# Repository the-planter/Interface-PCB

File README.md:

# Planter Interface PCB

Interface PCB for an automated hydroponics system, created using KiCad 6.0. 

This PCB enables control and interfacing a Raspberry with several liquid level sensors, 12V peristaltic pumps, a few temperature sensors, and remote controllable outlets.

This PCB acts as a carrier board for various off-the-shelf breakout boards. It enables noise-free signals, painless testing, and robust interfacing of the liquid level sensors, peristaltic pumps, air & water temperature sensors, and electrical outlets. Standardized connector types are used to guarantee secure connections; connector types are differentiated by their purpose and voltage level, to ensure no mismatch between components and voltage levels occur. The use of breakout boards alleviates the difficulties in procuring discrete Integrated Circuits (ICs) during the ongoing chip shortage. 

## Manufactured board

| Left View | Right View |
| :---: | :---: |
|  |  |

Hooked up to all sensors:

## Renders

## Routing

## Mechanical Team's Enclosure
The PCB is placed in the top shelf of the enclosure designed by the Mechanical Team

## Schematic

## Repo Setup
- Setup KiCad 6.0 using my [kicad-libraries](https://github.com/AbhinavA10/kicad-libraries)

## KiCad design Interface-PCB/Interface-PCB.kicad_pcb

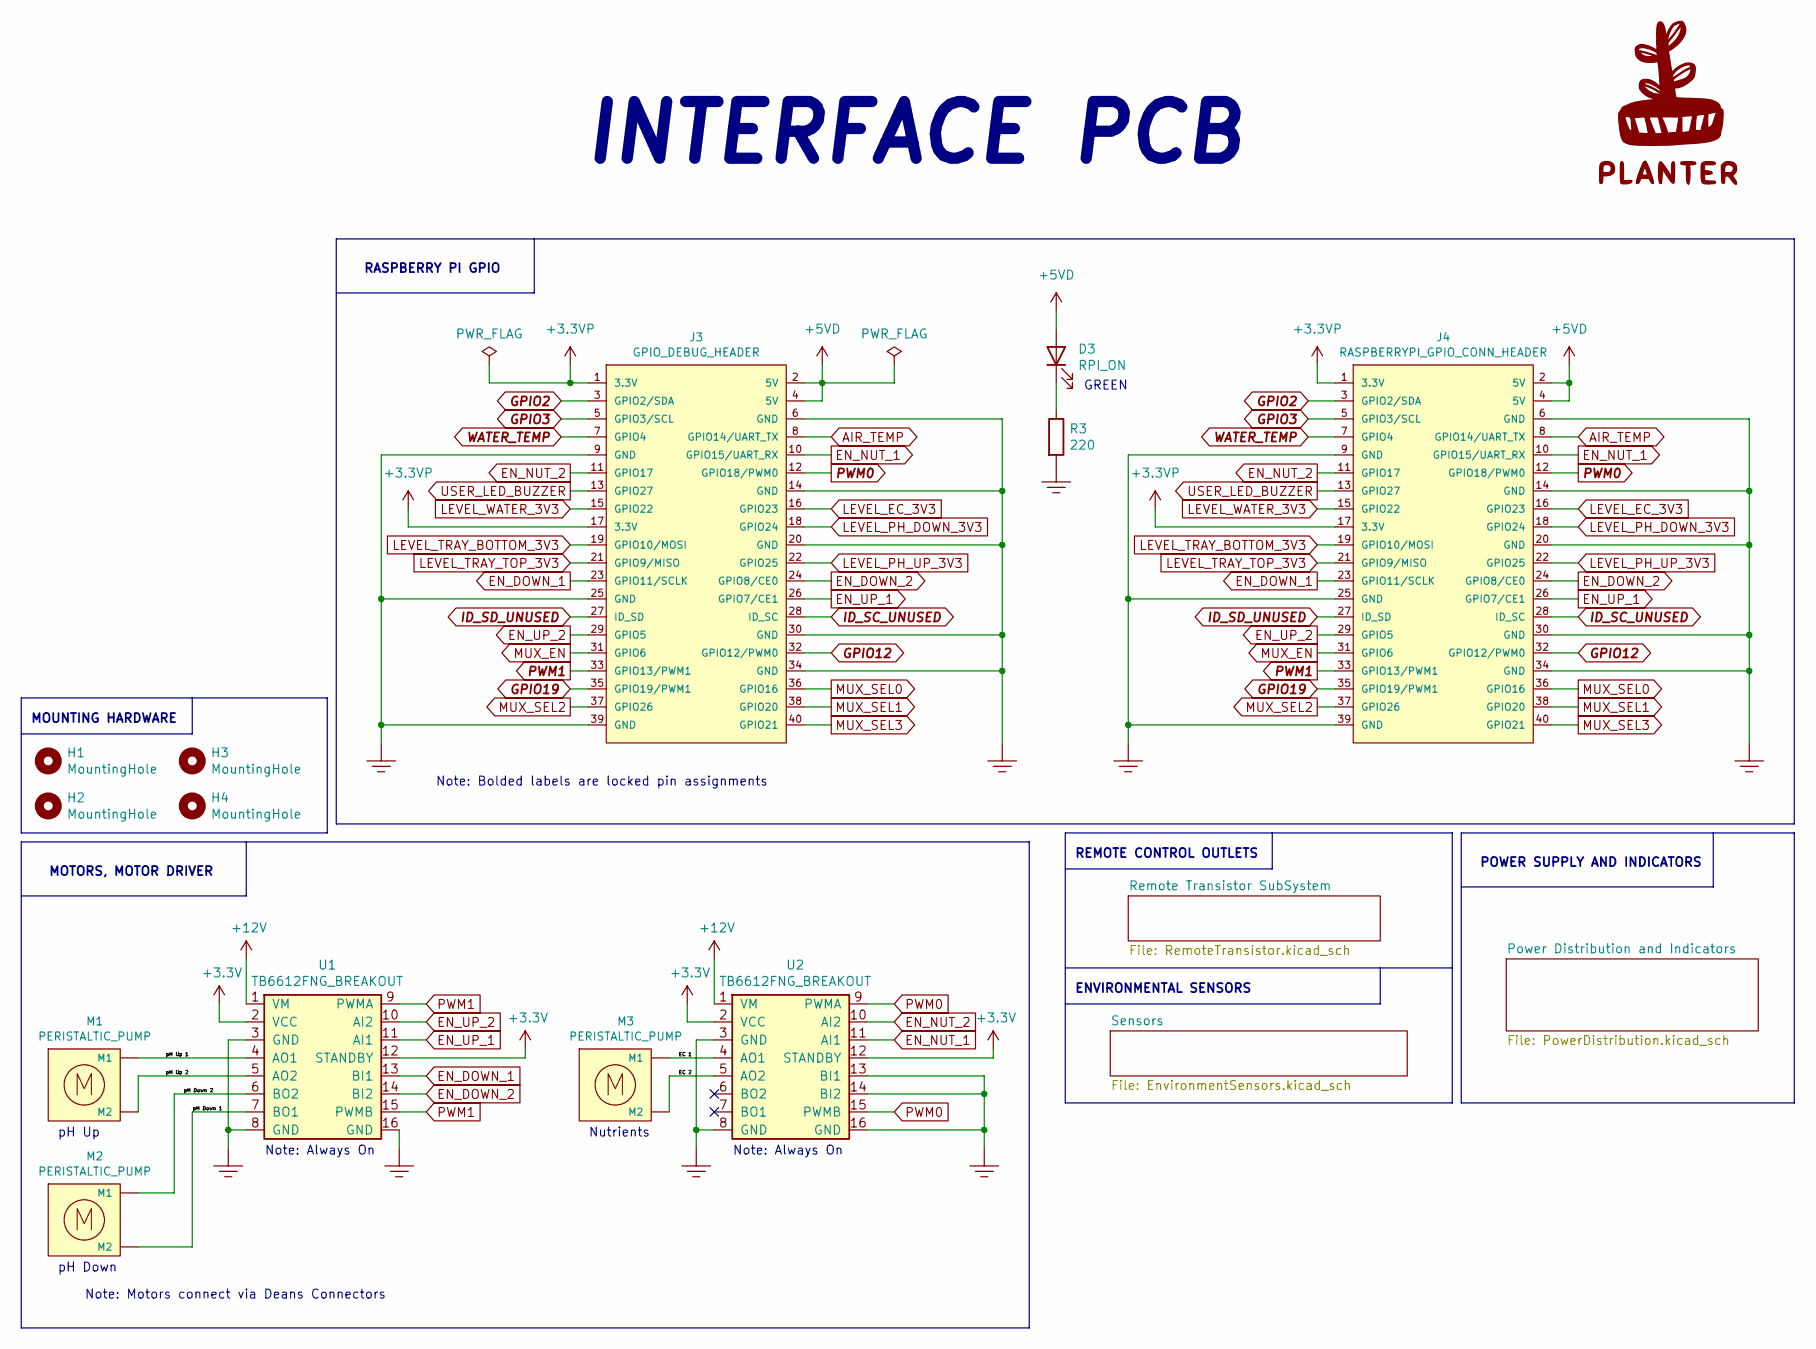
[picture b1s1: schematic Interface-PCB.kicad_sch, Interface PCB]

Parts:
D3: RPI_ON; LED_SS_1206_3216Metric_Pad1.42x1.75mm_HandSolder
G1: PLANTER_LOGO_8mm; PLANTER_LOGO_30MM_SILKSCREEN
H1, H2, H3, H4: MountingHole; MountingHole_3.2mm_M3_Pad
J3: GPIO_DEBUG_HEADER; RASPBERRYPI-40-PIN-GPIO-2x20_P2.54mm_Vertical
J4: RASPBERRYPI_GPIO_CONN_HEADER; RASPBERRYPI-40-PIN-GPIO-2x20_P2.54mm_Vertical
M1, M2, M3: PERISTALTIC_PUMP; PowerPad_Pair_5.0x5.0mm
R3: 220; R_SS_Axial_DIN0207_L6.3mm_D2.5mm_P10.16mm_Horizontal
U1, U2: TB6612FNG_BREAKOUT; TB6612FNG_Breakout; Digikey_Part_Number 1568-1755-ND

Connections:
+3.3VP: J3.1 (3.3V), J3.17 (3.3V), J4.1 (3.3V), J4.17 (3.3V); also elsewhere on the board
+3V3: U1.2 (VCC), U1.12 (STANDBY), U2.2 (VCC), U2.12 (STANDBY); also elsewhere on the board
+5VD: D3.2 (A), J3.2 (5V), J3.4 (5V), J4.2 (5V), J4.4 (5V); also elsewhere on the board
+12V: U1.1 (VM), U2.1 (VM); also elsewhere on the board
/EC 1: M3.1 (M1), U2.4 (AO1)
/EC 2: M3.2 (M2), U2.5 (AO2)
/pH Down 1: M2.2 (M2), U1.7 (BO1)
/pH Down 2: M2.1 (M1), U1.6 (BO2)
/pH Up 1: M1.1 (M1), U1.4 (AO1)
/pH Up 2: M1.2 (M2), U1.5 (AO2)
AIR_TEMP: J3.8 (GPIO14/UART_TX), J4.8 (GPIO14/UART_TX); also elsewhere on the board
EN_DOWN_1: J3.23 (GPIO11/SCLK), J4.23 (GPIO11/SCLK), U1.13 (BI1)
EN_DOWN_2: J3.24 (GPIO8/CE0), J4.24 (GPIO8/CE0), U1.14 (BI2)
EN_NUT_1: J3.10 (GPIO15/UART_RX), J4.10 (GPIO15/UART_RX), U2.11 (AI1)
EN_NUT_2: J3.11 (GPIO17), J4.11 (GPIO17), U2.10 (AI2)
EN_UP_1: J3.26 (GPIO7/CE1), J4.26 (GPIO7/CE1), U1.11 (AI1)
EN_UP_2: J3.29 (GPIO5), J4.29 (GPIO5), U1.10 (AI2)
GND: J3.6 (GND), J3.9 (GND), J3.14 (GND), J3.20 (GND), J3.25 (GND), J3.30 (GND), J3.34 (GND), J3.39 (GND), J4.6 (GND), J4.9 (GND), J4.14 (GND), J4.20 (GND), J4.25 (GND), J4.30 (GND), J4.34 (GND), J4.39 (GND), R3.2, U1.3 (GND), U1.8 (GND), U1.16 (GND), U2.3 (GND), U2.8 (GND), U2.13 (BI1), U2.14 (BI2), U2.16 (GND); also elsewhere on the board
GPIO2: J3.3 (GPIO2/SDA), J4.3 (GPIO2/SDA)
GPIO3: J3.5 (GPIO3/SCL), J4.5 (GPIO3/SCL)
GPIO12: J3.32 (GPIO12/PWM0), J4.32 (GPIO12/PWM0)
GPIO19: J3.35 (GPIO19/PWM1), J4.35 (GPIO19/PWM1)
ID_SC_UNUSED: J3.28 (ID_SC), J4.28 (ID_SC)
ID_SD_UNUSED: J3.27 (ID_SD), J4.27 (ID_SD)
LEVEL_EC_3V3: J3.16 (GPIO23), J4.16 (GPIO23); also elsewhere on the board
LEVEL_PH_DOWN_3V3: J3.18 (GPIO24), J4.18 (GPIO24); also elsewhere on the board
LEVEL_PH_UP_3V3: J3.22 (GPIO25), J4.22 (GPIO25); also elsewhere on the board
LEVEL_TRAY_BOTTOM_3V3: J3.19 (GPIO10/MOSI), J4.19 (GPIO10/MOSI); also elsewhere on the board
LEVEL_TRAY_TOP_3V3: J3.21 (GPIO9/MISO), J4.21 (GPIO9/MISO); also elsewhere on the board
LEVEL_WATER_3V3: J3.15 (GPIO22), J4.15 (GPIO22); also elsewhere on the board
MUX_EN: J3.31 (GPIO6), J4.31 (GPIO6); also elsewhere on the board
MUX_SEL0: J3.36 (GPIO16), J4.36 (GPIO16); also elsewhere on the board
MUX_SEL1: J3.38 (GPIO20), J4.38 (GPIO20); also elsewhere on the board
MUX_SEL2: J3.37 (GPIO26), J4.37 (GPIO26); also elsewhere on the board
MUX_SEL3: J3.40 (GPIO21), J4.40 (GPIO21); also elsewhere on the board
unnamed: D3.1 (K), R3.1
PWM0: J3.12 (GPIO18/PWM0), J4.12 (GPIO18/PWM0), U2.9 (PWMA), U2.15 (PWMB)
PWM1: J3.33 (GPIO13/PWM1), J4.33 (GPIO13/PWM1), U1.9 (PWMA), U1.15 (PWMB)
USER_LED_BUZZER: J3.13 (GPIO27), J4.13 (GPIO27); also elsewhere on the board
WATER_TEMP: J3.7 (GPIO4), J4.7 (GPIO4); also elsewhere on the board

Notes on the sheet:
pH Down
pH Up
Note: Motors connect via Deans Connectors
Note: Always On
POWER SUPPLY AND INDICATORS
MOUNTING HARDWARE
REMOTE CONTROL OUTLETS
Note: Bolded labels are locked pin assignments
GREEN
MOTORS, MOTOR DRIVER
RASPBERRY PI GPIO
ENVIRONMENTAL SENSORS
INTERFACE PCB
Nutrients

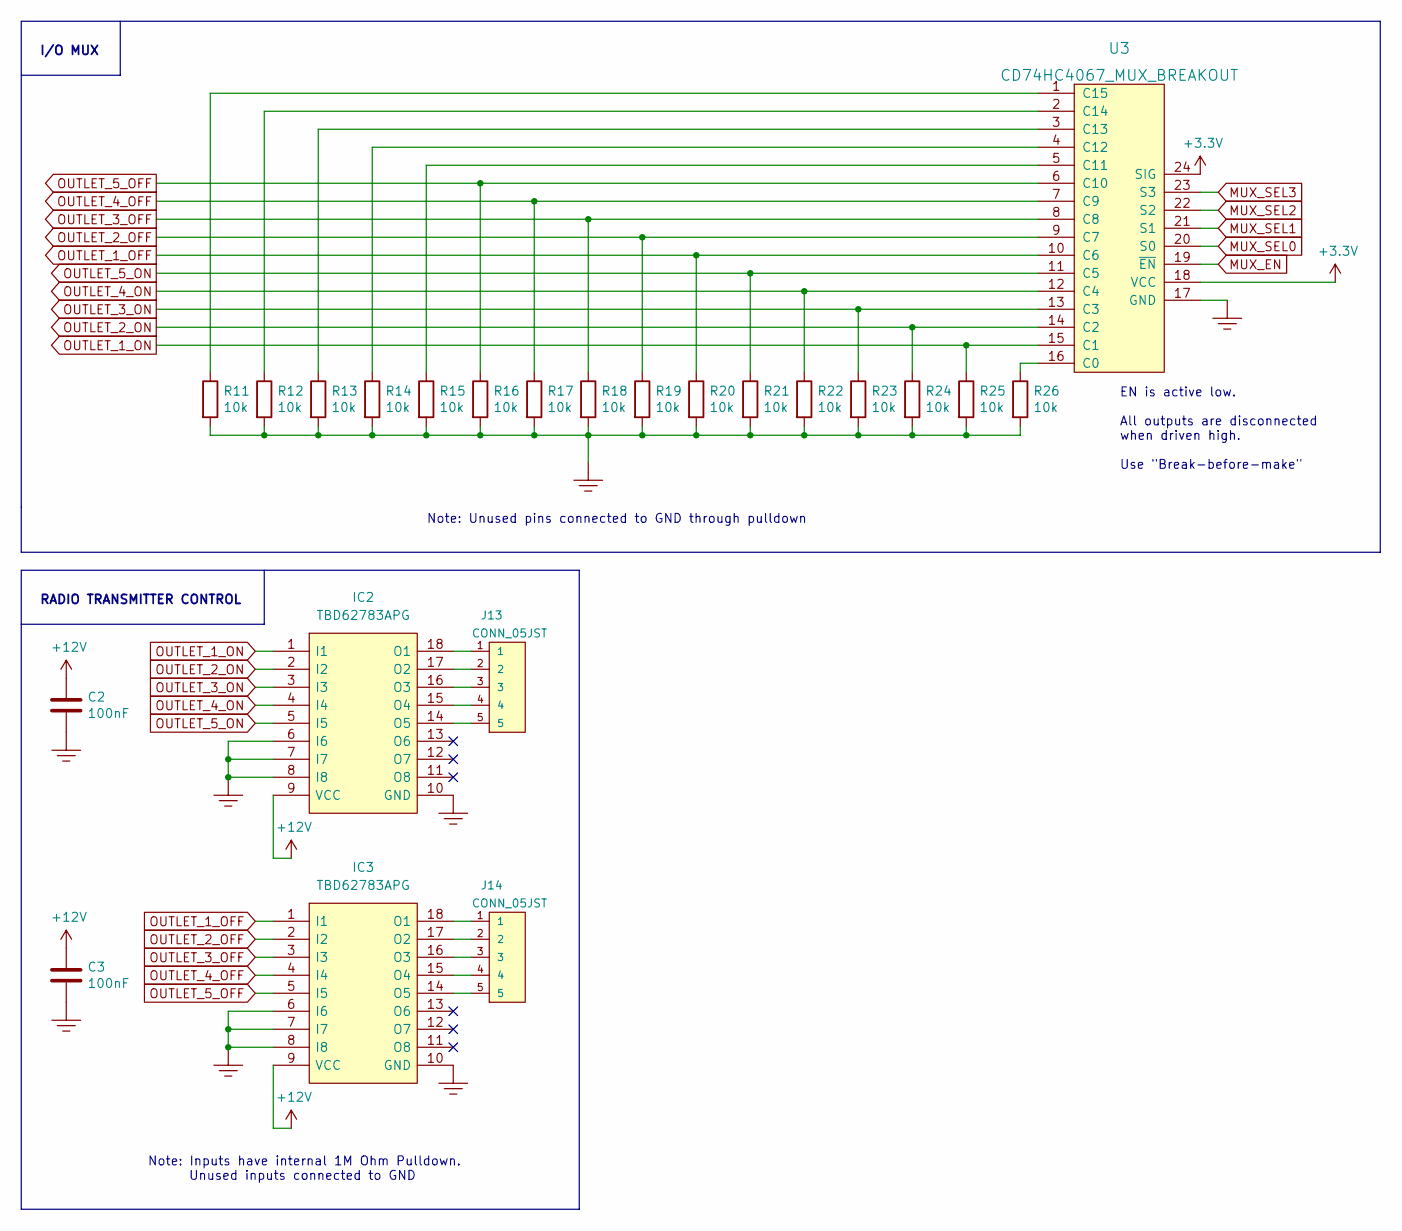
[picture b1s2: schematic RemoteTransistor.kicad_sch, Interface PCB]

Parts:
C2, C3: 100nF; C_Ceramic_Disc_D4.3mm_W1.9mm_P5.08mm
IC2, IC3: TBD62783APG; DIP-18_W7.62mm_Socket_IC; Digikey_Part_Number TBD62783APG-ND
J13, J14: CONN_05JST; JST_XH_1x05_P2.54mm_Vertical
R11, R12, R13, R14, R15, R16, R17, R18, R19, R20, R21, R22, R23, R24, R25, R26: 10k; R_SS_Axial_DIN0207_L6.3mm_D2.5mm_P10.16mm_Horizontal
U3: CD74HC4067_MUX_BREAKOUT; Digikey_Part_Number 1568-1181-ND

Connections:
+3V3: U3.18 (VCC), U3.24 (SIG); also elsewhere on the board
+12V: C2.1, C3.1, IC2.9 (VCC), IC3.9 (VCC); also elsewhere on the board
GND: C2.2, C3.2, IC2.6 (I6), IC2.7 (I7), IC2.8 (I8), IC2.10 (GND), IC3.6 (I6), IC3.7 (I7), IC3.8 (I8), IC3.10 (GND), R11.2, R12.2, R13.2, R14.2, R15.2, R16.2, R17.2, R18.2, R19.2, R20.2, R21.2, R22.2, R23.2, R24.2, R25.2, R26.2, U3.17 (GND); also elsewhere on the board
MUX_EN: U3.19 (~EN); also elsewhere on the board
MUX_SEL0: U3.20 (S0); also elsewhere on the board
MUX_SEL1: U3.21 (S1); also elsewhere on the board
MUX_SEL2: U3.22 (S2); also elsewhere on the board
MUX_SEL3: U3.23 (S3); also elsewhere on the board
unnamed: IC2.14 (O5), J13.5
unnamed: IC2.15 (O4), J13.4
unnamed: IC2.16 (O3), J13.3
unnamed: IC2.17 (O2), J13.2
unnamed: IC2.18 (O1), J13.1
unnamed: IC3.14 (O5), J14.5
unnamed: IC3.15 (O4), J14.4
unnamed: IC3.16 (O3), J14.3
unnamed: IC3.17 (O2), J14.2
unnamed: IC3.18 (O1), J14.1
unnamed: R11.1, U3.1 (C15)
unnamed: R12.1, U3.2 (C14)
unnamed: R13.1, U3.3 (C13)
unnamed: R14.1, U3.4 (C12)
unnamed: R15.1, U3.5 (C11)
unnamed: R26.1, U3.16 (C0)
OUTLET_1_OFF: IC3.1 (I1), R20.1, U3.10 (C6)
OUTLET_1_ON: IC2.1 (I1), R25.1, U3.15 (C1)
OUTLET_2_OFF: IC3.2 (I2), R19.1, U3.9 (C7)
OUTLET_2_ON: IC2.2 (I2), R24.1, U3.14 (C2)
OUTLET_3_OFF: IC3.3 (I3), R18.1, U3.8 (C8)
OUTLET_3_ON: IC2.3 (I3), R23.1, U3.13 (C3)
OUTLET_4_OFF: IC3.4 (I4), R17.1, U3.7 (C9)
OUTLET_4_ON: IC2.4 (I4), R22.1, U3.12 (C4)
OUTLET_5_OFF: IC3.5 (I5), R16.1, U3.6 (C10)
OUTLET_5_ON: IC2.5 (I5), R21.1, U3.11 (C5)

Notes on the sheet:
I/O MUX
Note: Unused pins connected to GND through pulldown
Note: Inputs have internal 1M Ohm Pulldown. Unused inputs connected to GND
RADIO TRANSMITTER CONTROL
EN is active low. All outputs are disconnected when driven high. Use "Break-before-make"

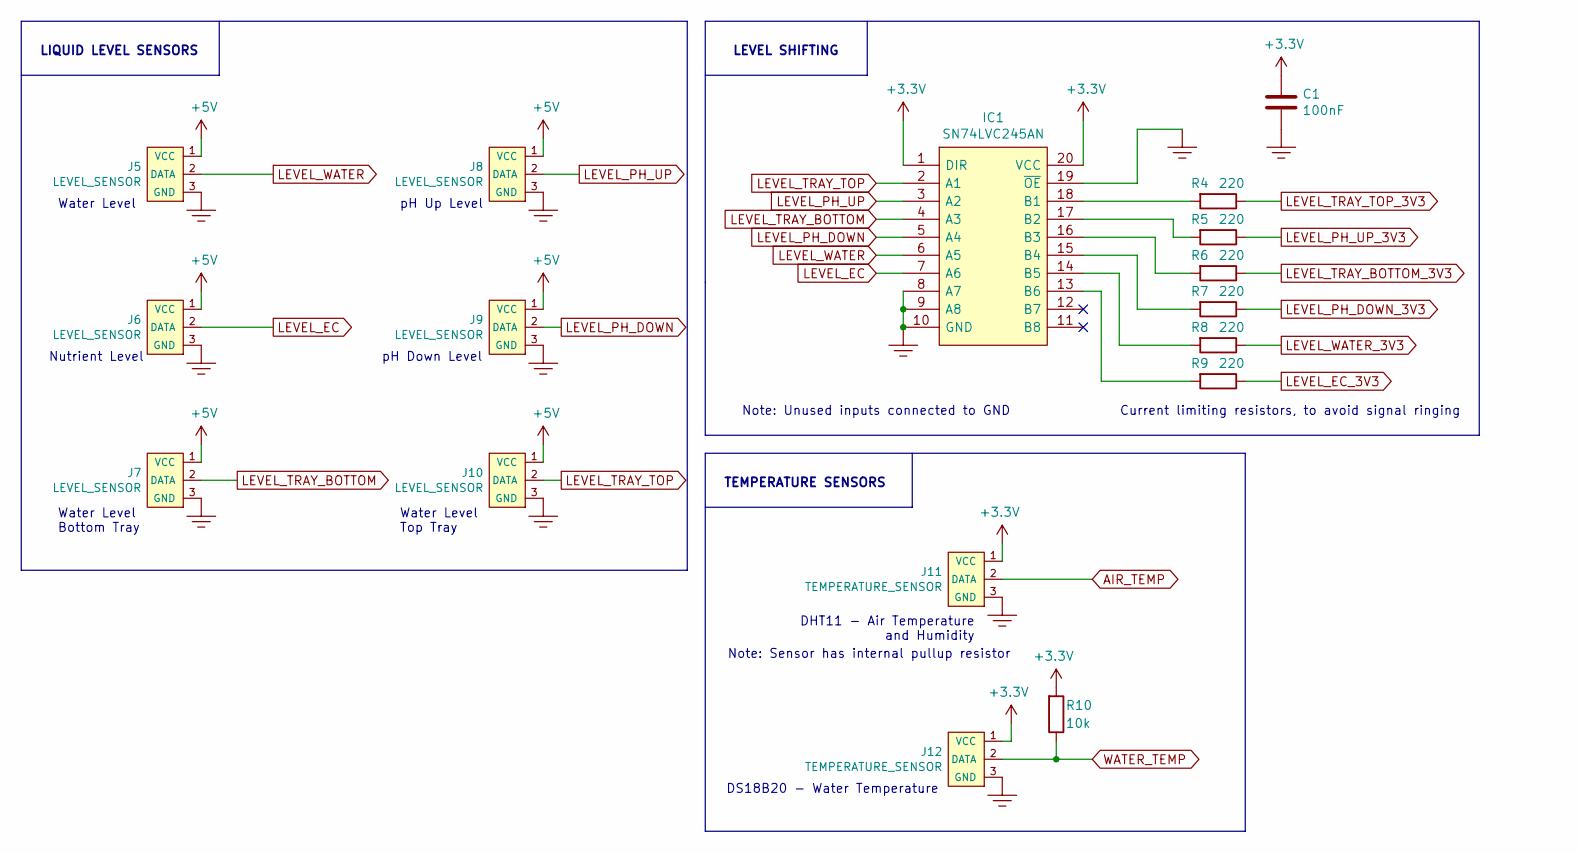
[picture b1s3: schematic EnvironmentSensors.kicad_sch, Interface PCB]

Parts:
C1: 100nF; C_Ceramic_Disc_D4.3mm_W1.9mm_P5.08mm
IC1: SN74LVC245AN; DIP-20_W7.62mm_Socket_IC; Digikey_Part_Number 296-8503-5-ND
J5, J6, J7, J8, J9, J10: LEVEL_SENSOR; JST_XH_1x03_P2.54mm_Vertical
J11, J12: TEMPERATURE_SENSOR; JST_XH_1x03_P2.54mm_Vertical
R4, R5, R6, R7, R8, R9: 220; R_SS_Axial_DIN0207_L6.3mm_D2.5mm_P10.16mm_Horizontal
R10: 10k; R_SS_Axial_DIN0207_L6.3mm_D2.5mm_P10.16mm_Horizontal

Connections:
+3V3: C1.1, IC1.1 (DIR), IC1.20 (VCC), J11.1 (VCC), J12.1 (VCC), R10.2; also elsewhere on the board
+5V: J5.1 (VCC), J6.1 (VCC), J7.1 (VCC), J8.1 (VCC), J9.1 (VCC), J10.1 (VCC); also elsewhere on the board
AIR_TEMP: J11.2 (DATA); also elsewhere on the board
GND: C1.2, IC1.8 (A7), IC1.9 (A8), IC1.10 (GND), IC1.19 (~OE), J5.3 (GND), J6.3 (GND), J7.3 (GND), J8.3 (GND), J9.3 (GND), J10.3 (GND), J11.3 (GND), J12.3 (GND); also elsewhere on the board
LEVEL_EC: IC1.7 (A6), J6.2 (DATA)
LEVEL_EC_3V3: R9.1; also elsewhere on the board
LEVEL_PH_DOWN: IC1.5 (A4), J9.2 (DATA)
LEVEL_PH_DOWN_3V3: R7.1; also elsewhere on the board
LEVEL_PH_UP: IC1.3 (A2), J8.2 (DATA)
LEVEL_PH_UP_3V3: R5.1; also elsewhere on the board
LEVEL_TRAY_BOTTOM: IC1.4 (A3), J7.2 (DATA)
LEVEL_TRAY_BOTTOM_3V3: R6.1; also elsewhere on the board
LEVEL_TRAY_TOP: IC1.2 (A1), J10.2 (DATA)
LEVEL_TRAY_TOP_3V3: R4.1; also elsewhere on the board
LEVEL_WATER: IC1.6 (A5), J5.2 (DATA)
LEVEL_WATER_3V3: R8.1; also elsewhere on the board
unnamed: IC1.13 (B6), R9.2
unnamed: IC1.14 (B5), R8.2
unnamed: IC1.15 (B4), R7.2
unnamed: IC1.16 (B3), R6.2
unnamed: IC1.17 (B2), R5.2
unnamed: IC1.18 (B1), R4.2
WATER_TEMP: J12.2 (DATA), R10.1; also elsewhere on the board

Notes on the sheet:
Water Level Top Tray
pH Down Level
DHT11 - Air Temperature and Humidity
Nutrient Level
LIQUID LEVEL SENSORS
Water Level
LEVEL SHIFTING
Note: Unused inputs connected to GND
TEMPERATURE SENSORS
Water Level Bottom Tray
pH Up Level
DS18B20 - Water Temperature
Note: Sensor has internal pullup resistor
Current limiting resistors, to avoid signal ringing

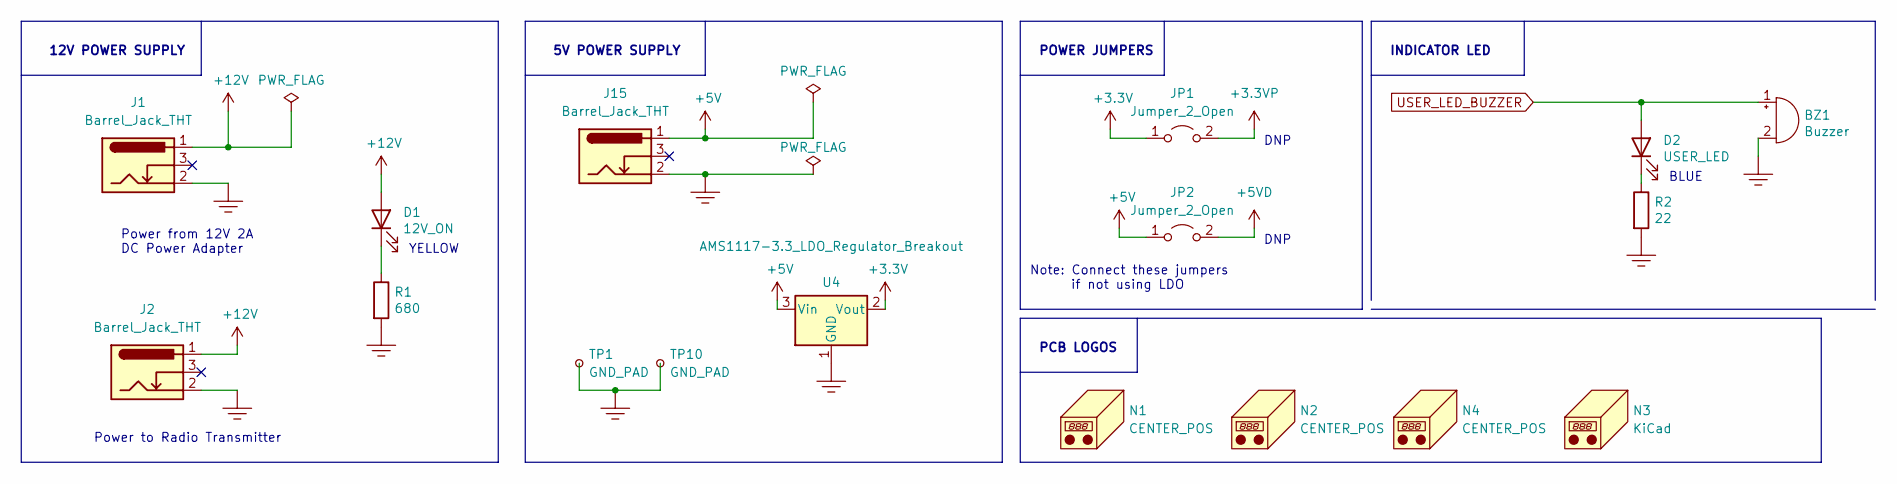
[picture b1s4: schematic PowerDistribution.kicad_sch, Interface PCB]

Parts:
BZ1: Buzzer; Buzzer_Generic_D12.2mm_H6.5mm
D1: 12V_ON; LED_SS_1206_3216Metric_Pad1.42x1.75mm_HandSolder
D2: USER_LED; LED_SS_1206_3216Metric_Pad1.42x1.75mm_HandSolder
J1, J2, J15: Barrel_Jack_THT; BarrelJack_Horizontal
JP1, JP2: Jumper_2_Open; R_SS_Axial_DIN0207_L6.3mm_D2.5mm_P10.16mm_Horizontal
N1, N2, N4: CENTER_POS; Polarity_Center_Positive_7.5mm_SilkScreen
N3: KiCad; KiCad-Logo2_8mm_SilkScreen
R1: 680; R_SS_Axial_DIN0207_L6.3mm_D2.5mm_P10.16mm_Horizontal
R2: 22; R_SS_Axial_DIN0207_L6.3mm_D2.5mm_P10.16mm_Horizontal
TP1, TP10: GND_PAD; TestPoint_Pad_5.0x5.0mm
U4: AMS1117-3.3_LDO_Regulator_Breakout; AMS1117-3.3_LDO_Regulator_Breakout_Board

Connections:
+3.3VP: JP1.2 (B); also elsewhere on the board
+3V3: JP1.1 (A), U4.2 (Vout); also elsewhere on the board
+5V: J15.1, JP2.1 (A), U4.3 (Vin); also elsewhere on the board
+5VD: JP2.2 (B); also elsewhere on the board
+12V: D1.2 (A), J1.1, J2.1; also elsewhere on the board
GND: BZ1.2 (+), J1.2, J2.2, J15.2, R1.2, R2.2, TP1.1, TP10.1, U4.1 (GND); also elsewhere on the board
unnamed: D1.1 (K), R1.1
unnamed: D2.1 (K), R2.1
USER_LED_BUZZER: BZ1.1 (-), D2.2 (A); also elsewhere on the board

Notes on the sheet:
POWER JUMPERS
Power from 12V 2A DC Power Adapter
YELLOW
DNP
INDICATOR LED
12V POWER SUPPLY
Note: Connect these jumpers if not using LDO
BLUE
5V POWER SUPPLY
PCB LOGOS
Power to Radio Transmitter

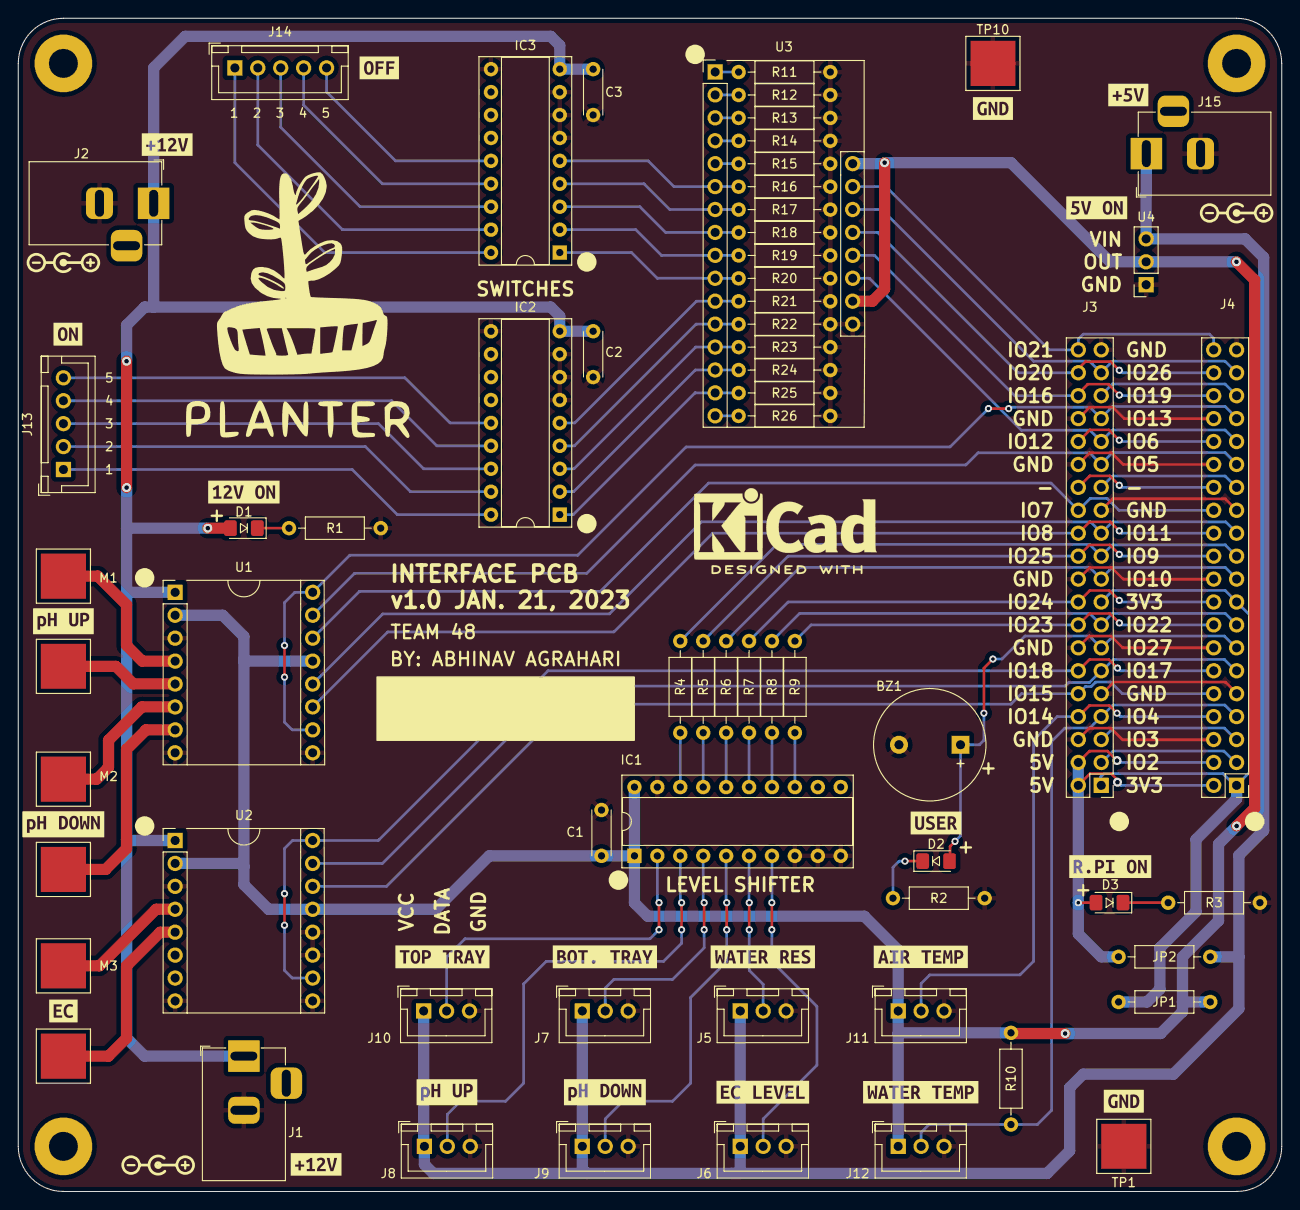
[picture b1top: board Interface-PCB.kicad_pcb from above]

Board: 2 copper layers, 140.0 x 130.0 mm, 93 parts (0 on the bottom side), 81 nets.

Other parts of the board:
kibuzzard-63CB80E4: G***; kibuzzard-63CB80E4
kibuzzard-63CB87CD: G***; kibuzzard-63CB87CD
kibuzzard-63CB87D2: G***; kibuzzard-63CB87D2
kibuzzard-63CB811C: G***; kibuzzard-63CB811C
kibuzzard-63CB813E: G***; kibuzzard-63CB813E
kibuzzard-63CB856E: G***; kibuzzard-63CB856E
kibuzzard-63CB864A: G***; kibuzzard-63CB864A
kibuzzard-63CB8107, kibuzzard-63CB8107#2: G***; kibuzzard-63CB8107
kibuzzard-63CB8123: G***; kibuzzard-63CB8123
kibuzzard-63CB8136: G***; kibuzzard-63CB8136
kibuzzard-63CB8267: G***; kibuzzard-63CB8267
kibuzzard-63CB8415: G***; kibuzzard-63CB8415
kibuzzard-63CB8663, kibuzzard-63CB8663#2: G***; kibuzzard-63CB8663
kibuzzard-63CB8737, kibuzzard-63CB8737#2: G***; kibuzzard-63CB8737
kibuzzard-63CBAC35: G***; kibuzzard-63CBAC35
kibuzzard-63CC71CC: G***; kibuzzard-63CC71CC
kibuzzard-63CC577E: G***; kibuzzard-63CC577E
kibuzzard-63CDEE5A: G***; kibuzzard-63CDEE5A
kibuzzard-63CDEE7D: G***; kibuzzard-63CDEE7D

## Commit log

2022-11-15 First draft
2022-11-15 Split schematic sheets
2022-11-16 Initial layout for FDP
2022-11-20 Assign misc footprints for FDP
2022-12-04 Change to Highside switch
2023-01-08 Add diagrams and datasheets
2023-01-08 Review Schematic
2023-01-08 Add indicator LEDs
2023-01-08 Reorder Remote Transistors
2023-01-08 Upgrade project to KiCad 6
2023-01-10 Update schematic based on breadboard tests
    - Add current limiting resistors to Level Shifter output
    - Add pull down resistors on all Mux outputs
2023-01-19 Setup JLCPCB Plotting Rules
2023-01-19 Add test points and pads
2023-01-19 Add Planter Logo to schematic
2023-01-20 Add footprints for pads
2023-01-20 Add breakout board and IC footprints
    - MUX
    - Motor Driver
    - PDIP ICs
    - LEDs
2023-01-20 Add JST Connector Footprints
2023-01-20 Update Header pin and Buzzer Footprints
2023-01-20 Add JLC design rules
2023-01-21 Complete Initial Layout of PCB
    - aligned to 5mm grid
    - 100x100mm board
    - update footprints
    - align 2 resistors to 2.54mm spacing
2023-01-21 Increase board size, Add connector labels
    - Increase board size to 140x130mm
    - Refine layout on PCB
    - Align breakout board resistors to 2.54mm spacing
    - Add Inverted silkscreen labels for off-board connectors
2023-01-21 Create ground plane, swap motor driver pins
    - Create Ground pour/plane on F.Copper
    - Swap motor driver pin assignments, to resolve some route
    criss-crossing
2023-01-21 Align DIP-socket resistors with 2.54mm pin spacing
2023-01-21 Complete PCB layout
    - Complete component positioning and PCB layout
    - Swap most pin assignments to resolve track route criss-crossing
2023-01-21 Update Blue LED resistor value
2023-01-21 Update symbols from library
2023-01-21 Update JLCPCB DRC
2023-01-22 Add silkscreen and logos to PCB
    Complete silkscreen layer on PCB
2023-01-22 Swap more pin assignments
2023-01-22 Complete PCB routing
    - Complete routing of all tracks
    - DRC shows no errors, only non-warnings for kicad-buzzard related items
    - Remove Level Sensor test points
2023-01-22 Add Gerber and PDF exports
2023-01-23 Add 3.3V LDO Regulator and Barrel Jack Connectors
    - Add mounted barrel jack connectors for 12V and 5V
    - Add 5V to 3.3V LDO breakout board
    - Adjust silkscreen
    - Export and verify Gerbers
2023-01-23 Add rendered images
2023-01-23 Move Remote Control Barrel Jack
    - Move a barrel jack
    - Export Gerbers again
    - Update images
2023-01-25 Add PDF outputs of PCB and SVG output of schematic
2023-01-28 Remove outdated diagram
2023-02-21 Start Rev 1.1, Add pulldowns on Mux Input
2023-02-22 Update README with images of manufactured PCB
2023-03-11 Add description
